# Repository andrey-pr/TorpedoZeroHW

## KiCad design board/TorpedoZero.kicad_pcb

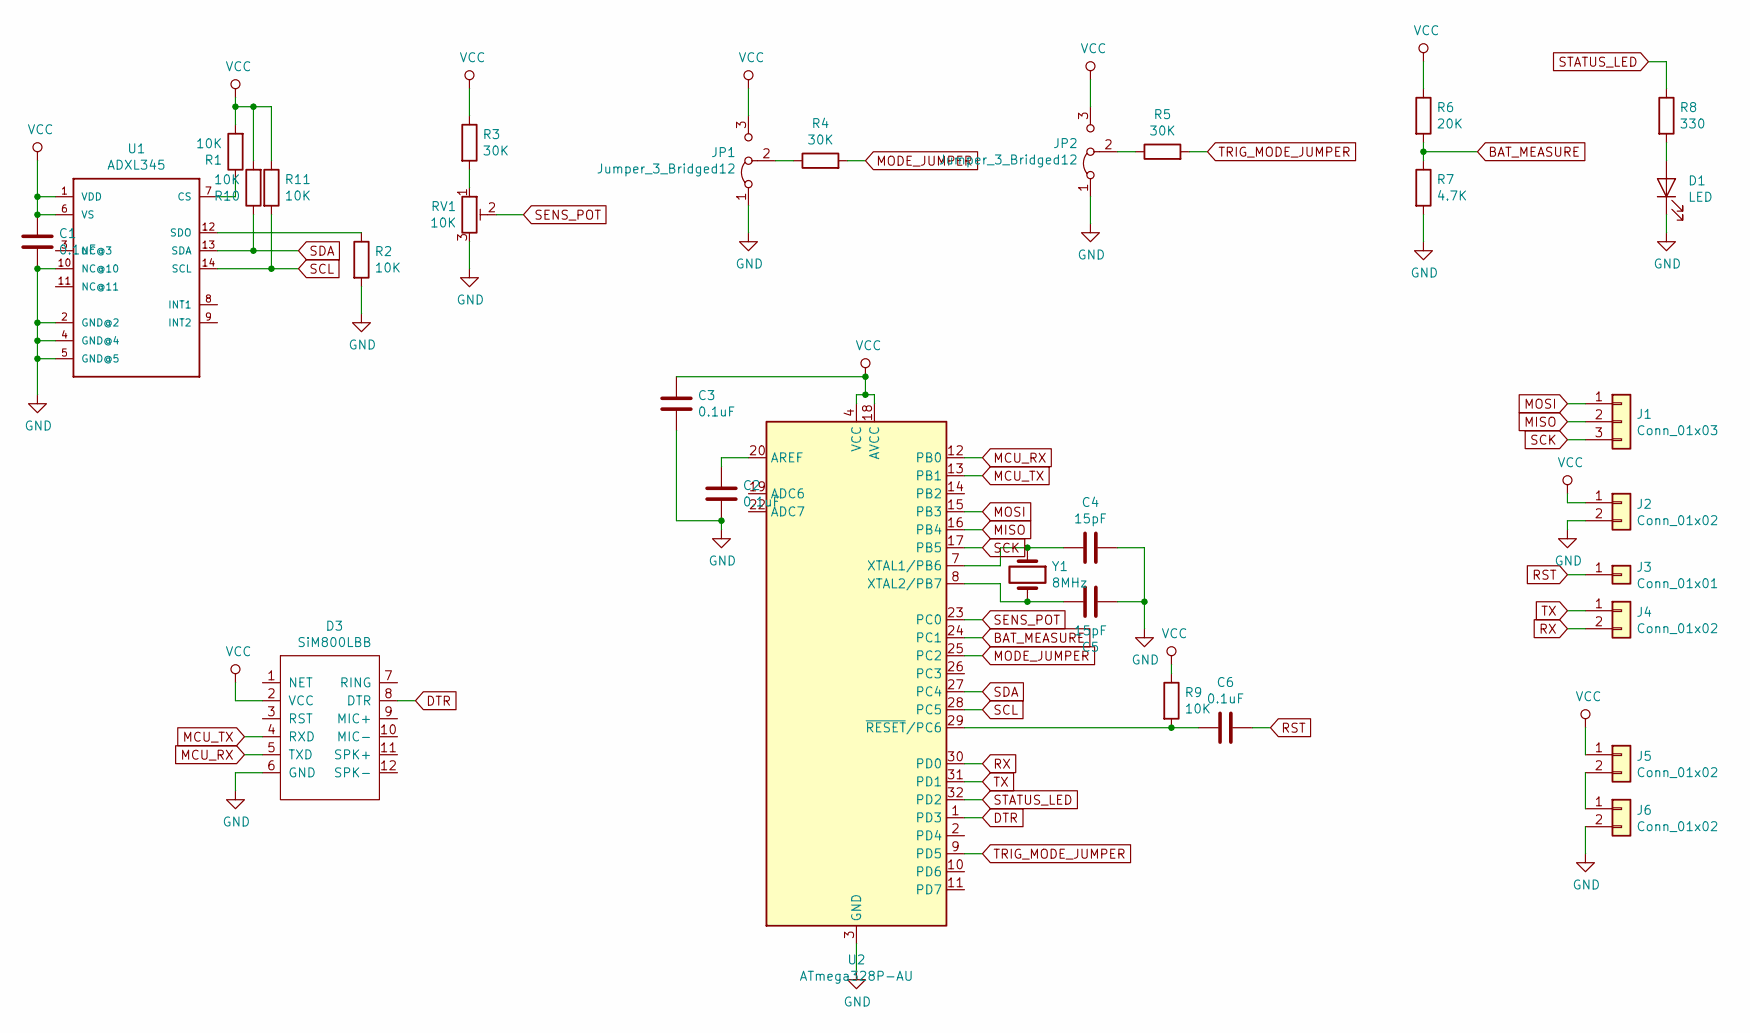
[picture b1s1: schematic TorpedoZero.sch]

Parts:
C1, C2, C3, C6: 0.1uF; C_0805_2012Metric_Pad1.15x1.40mm_HandSolder
C4, C5: 15pF; C_0805_2012Metric_Pad1.15x1.40mm_HandSolder
D1: LED; LED_1206_3216Metric_Pad1.42x1.75mm_HandSolder
D3: SiM800LBB; SIM800lBB
J1: Conn_01x03; PinHeader_1x03_P2.54mm_Vertical
J2, J4, J5, J6: Conn_01x02; PinHeader_1x02_P2.54mm_Vertical
J3: Conn_01x01; PinHeader_1x01_P2.54mm_Vertical
JP1, JP2: Jumper_3_Bridged12; PinHeader_1x03_P2.54mm_Vertical
R1, R2, R9, R10, R11: 10K; R_0805_2012Metric_Pad1.15x1.40mm_HandSolder
R3, R4, R5: 30K; R_0805_2012Metric_Pad1.15x1.40mm_HandSolder
R6: 20K; R_0805_2012Metric_Pad1.15x1.40mm_HandSolder
R7: 4.7K; R_0805_2012Metric_Pad1.15x1.40mm_HandSolder
R8: 330; R_0805_2012Metric_Pad1.15x1.40mm_HandSolder
RV1: 10K; Potentiometer_Bourns_3296W_Vertical
U1: ADXL345; LGA-14
U2: ATmega328P-AU; TQFP-32_7x7mm_P0.8mm
Y1: 8MHz; Crystal_HC49-U_Vertical

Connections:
BAT_MEASURE: R6.2, R7.1, U2.24 (PC1)
DTR: D3.8 (DTR), U2.1 (PD3)
GND: C1.2, C2.1, C3.1, C4.1, C5.2, D1.1 (K), D3.6 (GND), J2.2, J6.2, JP1.1 (A), JP2.1 (A), R2.2, R7.2, RV1.3, U1.2 (GND@2), U1.4 (GND@4), U1.5 (GND@5), U1.10 (NC@10), U2.3 (GND), U2.5 (GND), U2.21 (GND)
MCU_RX: D3.5 (TXD), U2.12 (PB0)
MCU_TX: D3.4 (RXD), U2.13 (PB1)
MISO: J1.2, U2.16 (PB4)
MODE_JUMPER: R4.2, U2.25 (PC2)
MOSI: J1.1, U2.15 (PB3)
unnamed: C2.2, U2.20 (AREF)
unnamed: C4.2, U2.7 (XTAL1/PB6), Y1.1
unnamed: C5.1, U2.8 (XTAL2/PB7), Y1.2
unnamed: C6.2, R9.2, U2.29 (~RESET~/PC6)
unnamed: D1.2 (A), R8.2
unnamed: J5.2, J6.1
unnamed: JP1.2 (C), R4.1
unnamed: JP2.2 (C), R5.1
unnamed: R1.1, U1.7 (CS)
unnamed: R2.1, U1.12 (SDO)
unnamed: R3.2, RV1.1
RST: C6.1, J3.1; also elsewhere on the board
RX: J4.2, U2.30 (PD0)
SCK: J1.3, U2.17 (PB5)
SCL: R11.2, U1.14 (SCL), U2.28 (PC5)
SDA: R10.1, U1.13 (SDA), U2.27 (PC4)
SENS_POT: RV1.2, U2.23 (PC0)
STATUS_LED: R8.1, U2.32 (PD2)
TRIG_MODE_JUMPER: R5.2, U2.9 (PD5)
TX: J4.1, U2.31 (PD1)
VCC: C1.1, C3.2, D3.2 (VCC), J2.1, J5.1, JP1.3 (B), JP2.3 (B), R1.2, R3.1, R6.1, R9.1, R10.2, R11.1, U1.1 (VDD), U1.6 (VS), U2.4 (VCC), U2.6 (VCC), U2.18 (AVCC)

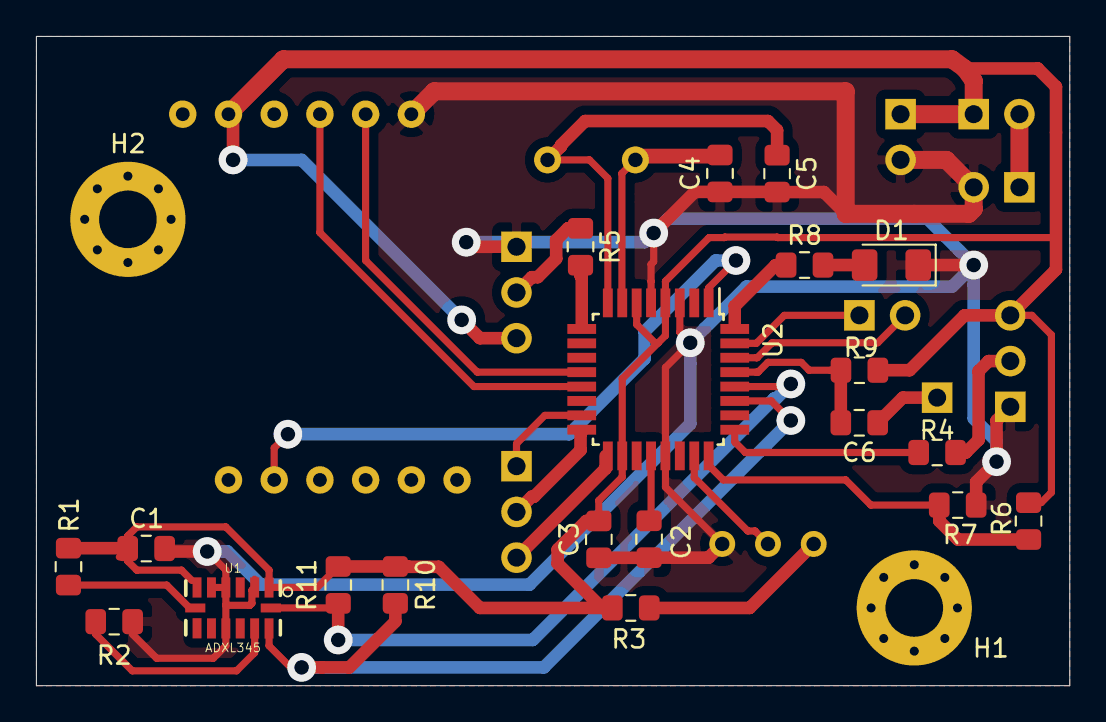
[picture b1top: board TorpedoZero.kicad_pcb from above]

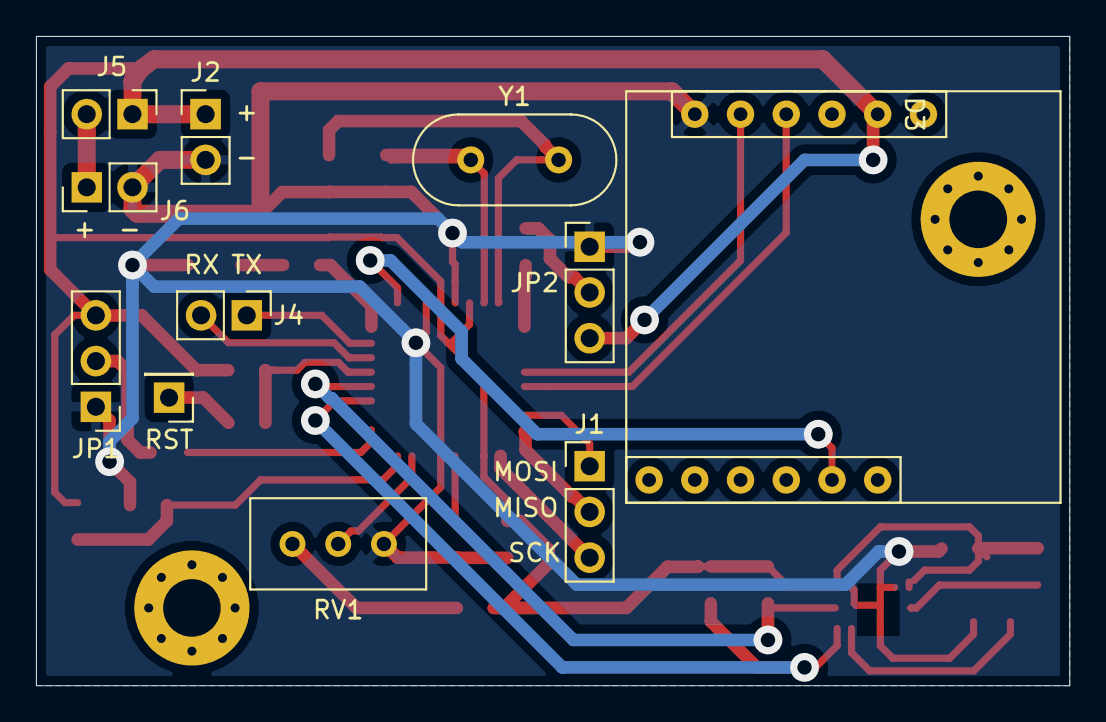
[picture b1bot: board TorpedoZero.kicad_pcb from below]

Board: 2 copper layers, 57.4 x 36.1 mm, 33 parts (11 on the bottom side), 29 nets.

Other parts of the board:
H1, H2: 3.2mm; MountingHole_3.2mm_M3_Pad_Via
RST: Conn_01x01; PinHeader_1x01_P2.54mm_Vertical

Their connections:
RST: RST.1; also elsewhere on the board
